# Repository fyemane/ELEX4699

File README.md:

# ELEX4699
ELEX4699 Elec System Design Project

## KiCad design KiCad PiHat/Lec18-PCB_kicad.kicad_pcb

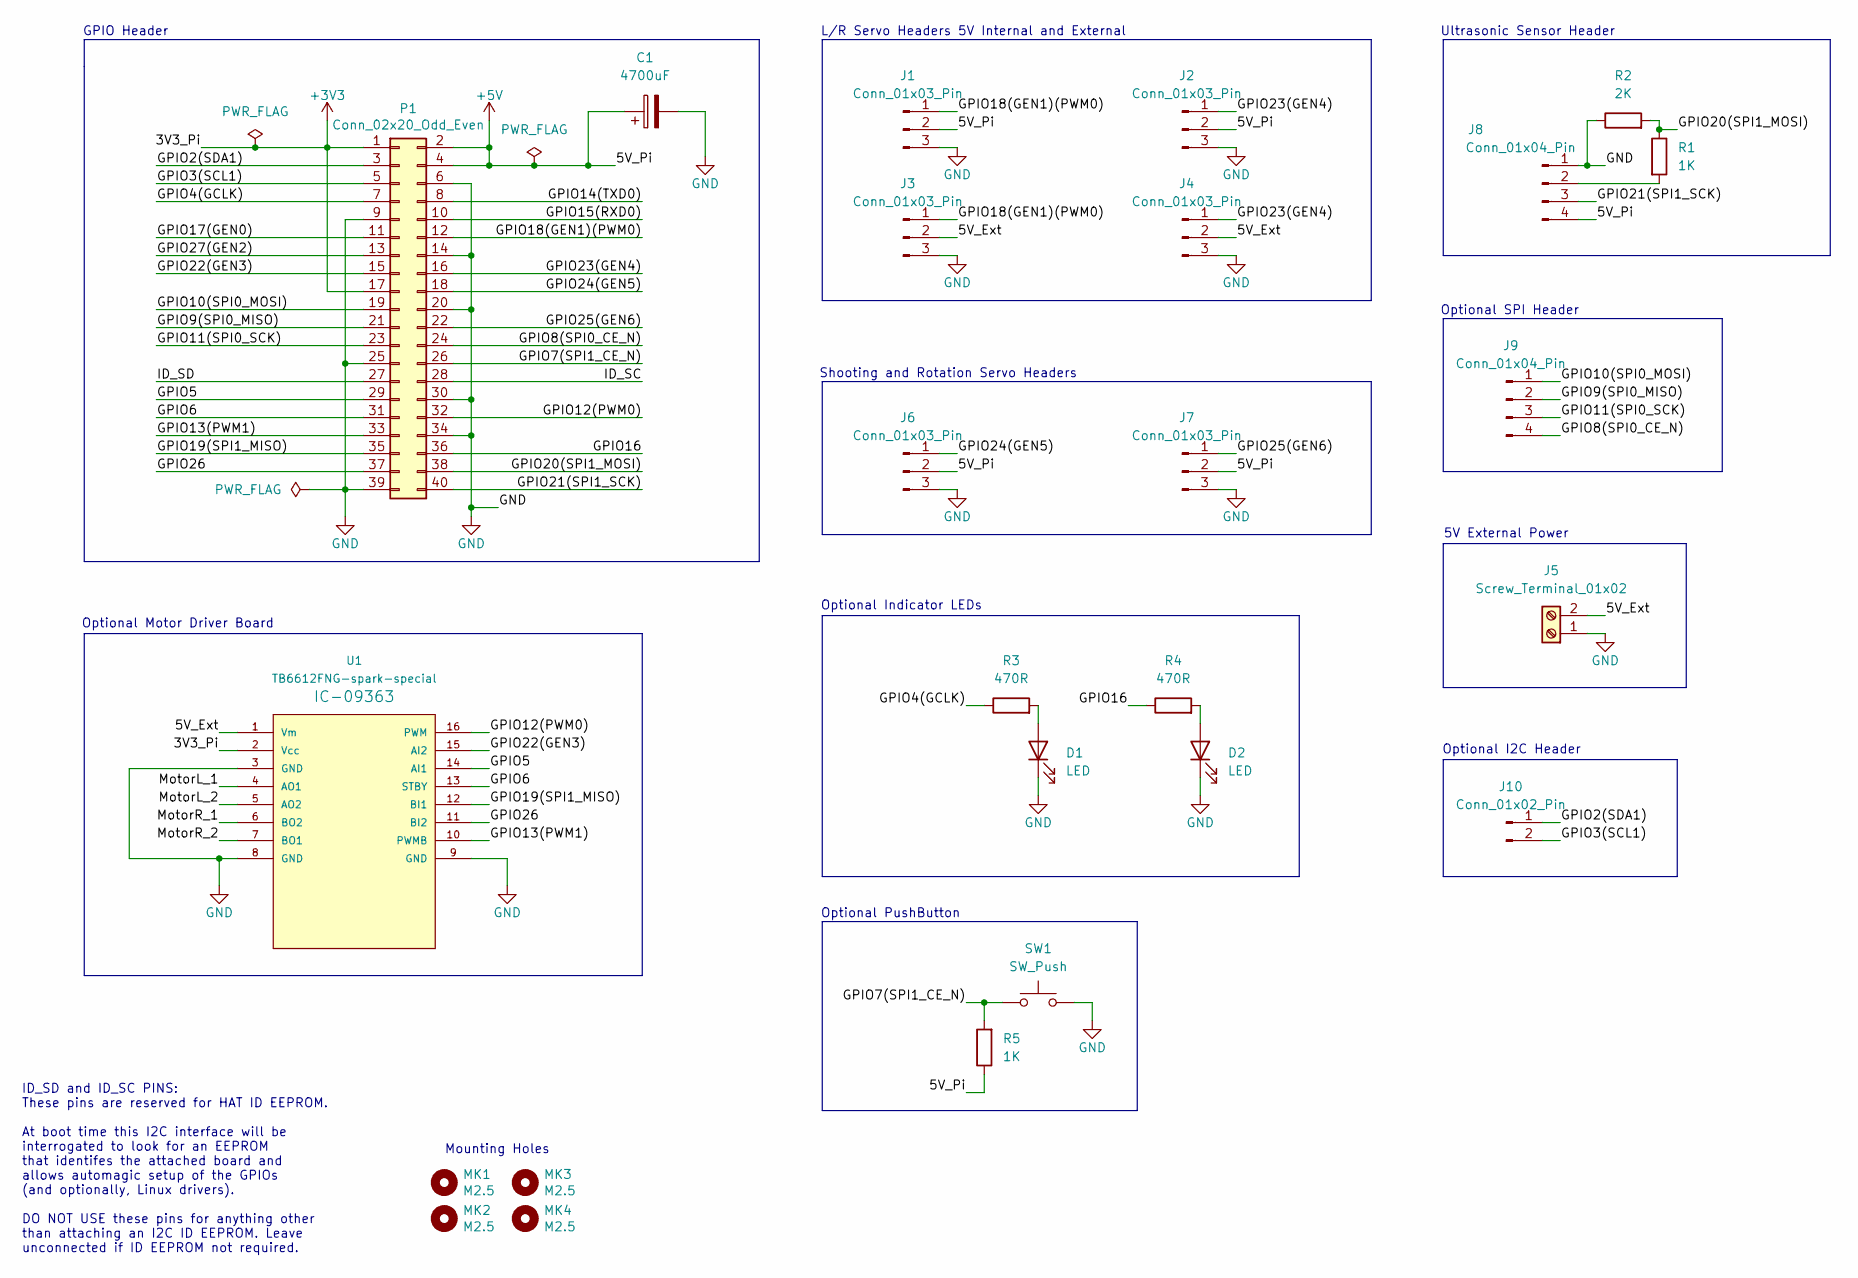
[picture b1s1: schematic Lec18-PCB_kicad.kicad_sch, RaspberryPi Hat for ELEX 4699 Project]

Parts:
C1: 4700uF; CP_Radial_D10.0mm_P7.50mm
D1, D2: LED; LED_D5.0mm
J1, J2, J3, J4, J6, J7: Conn_01x03_Pin; PinHeader_1x03_P2.54mm_Vertical
J5: Screw_Terminal_01x02; TerminalBlock_bornier-2_P5.08mm
J8, J9: Conn_01x04_Pin; PinHeader_1x04_P2.54mm_Vertical
J10: Conn_01x02_Pin; PinHeader_1x02_P2.54mm_Vertical
MK1, MK2, MK3, MK4: M2.5; MountingHole_2.7mm_M2.5
P1: Conn_02x20_Odd_Even; PinSocket_2x20_P2.54mm_Vertical
R1, R5: 1K; R_Axial_DIN0207_L6.3mm_D2.5mm_P10.16mm_Horizontal
R2: 2K; R_Axial_DIN0207_L6.3mm_D2.5mm_P10.16mm_Horizontal
R3, R4: 470R; R_Axial_DIN0207_L6.3mm_D2.5mm_P10.16mm_Horizontal
SW1: SW_Push; SW_PUSH_6mm_H5mm
U1: TB6612FNG-spark-special; MODULE_ROB-14450

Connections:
+3V3: P1.1, P1.17, U1.2 (Vcc)
+5V: C1.1, J1.2, J2.2, J6.2, J7.2, J8.4, P1.2, P1.4, R5.1
/5V_Ext: J3.2, J4.2, J5.2, U1.1 (Vm)
/GPIO2(SDA1): J10.1, P1.3
/GPIO3(SCL1): J10.2, P1.5
/GPIO4(GCLK): P1.7, R3.1
/GPIO5: P1.29, U1.14 (AI1)
/GPIO6: P1.31, U1.13 (STBY)
/GPIO7(SPI1_CE_N): P1.26, R5.2, SW1.1
/GPIO8(SPI0_CE_N): J9.4, P1.24
/GPIO9(SPI0_MISO): J9.2, P1.21
/GPIO10(SPI0_MOSI): J9.1, P1.19
/GPIO11(SPI0_SCK): J9.3, P1.23
/GPIO12(PWM0): P1.32, U1.16 (PWM)
/GPIO13(PWM1): P1.33, U1.10 (PWMB)
/GPIO14(TXD0): P1.8
/GPIO15(RXD0): P1.10
/GPIO16: P1.36, R4.1
/GPIO17(GEN0): P1.11
/GPIO18(GEN1)(PWM0): J1.1, J3.1, P1.12
/GPIO19(SPI1_MISO): P1.35, U1.12 (BI1)
/GPIO20(SPI1_MOSI): P1.38, R1.1, R2.2
/GPIO21(SPI1_SCK): J8.3, P1.40
/GPIO22(GEN3): P1.15, U1.15 (AI2)
/GPIO23(GEN4): J2.1, J4.1, P1.16
/GPIO24(GEN5): J6.1, P1.18
/GPIO25(GEN6): J7.1, P1.22
/GPIO26: P1.37, U1.11 (BI2)
/GPIO27(GEN2): P1.13
/ID_SC: P1.28
/ID_SD: P1.27
/MotorL_1: U1.4 (AO1)
/MotorL_2: U1.5 (AO2)
/MotorR_1: U1.6 (BO2)
/MotorR_2: U1.7 (BO1)
GND: C1.2, D1.1 (K), D2.1 (K), J1.3, J2.3, J3.3, J4.3, J5.1, J6.3, J7.3, J8.1, P1.6, P1.9, P1.14, P1.20, P1.25, P1.30, P1.34, P1.39, R2.1, SW1.2, U1.3 (GND), U1.8 (GND), U1.9 (GND)
unnamed: D1.2 (A), R3.2
unnamed: D2.2 (A), R4.2
unnamed: J8.2, R1.2

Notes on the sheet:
Optional SPI Header
Ultrasonic Sensor Header
Optional I2C Header
GPIO Header
L/R Servo Headers 5V Internal and External
5V External Power
ID_SD and ID_SC PINS: These pins are reserved for HAT ID EEPROM. At boot time this I2C interface will be interrogated to look for an EEPROM that identifes the attached board and allows automagic setup of the GPIOs (and optionally, Linux drivers). DO NOT USE these pins for anything other than attach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
Optional Motor Driver Board
Optional Indicator LEDs
Optional PushButton
Mounting Holes
Shooting and Rotation Servo Headers

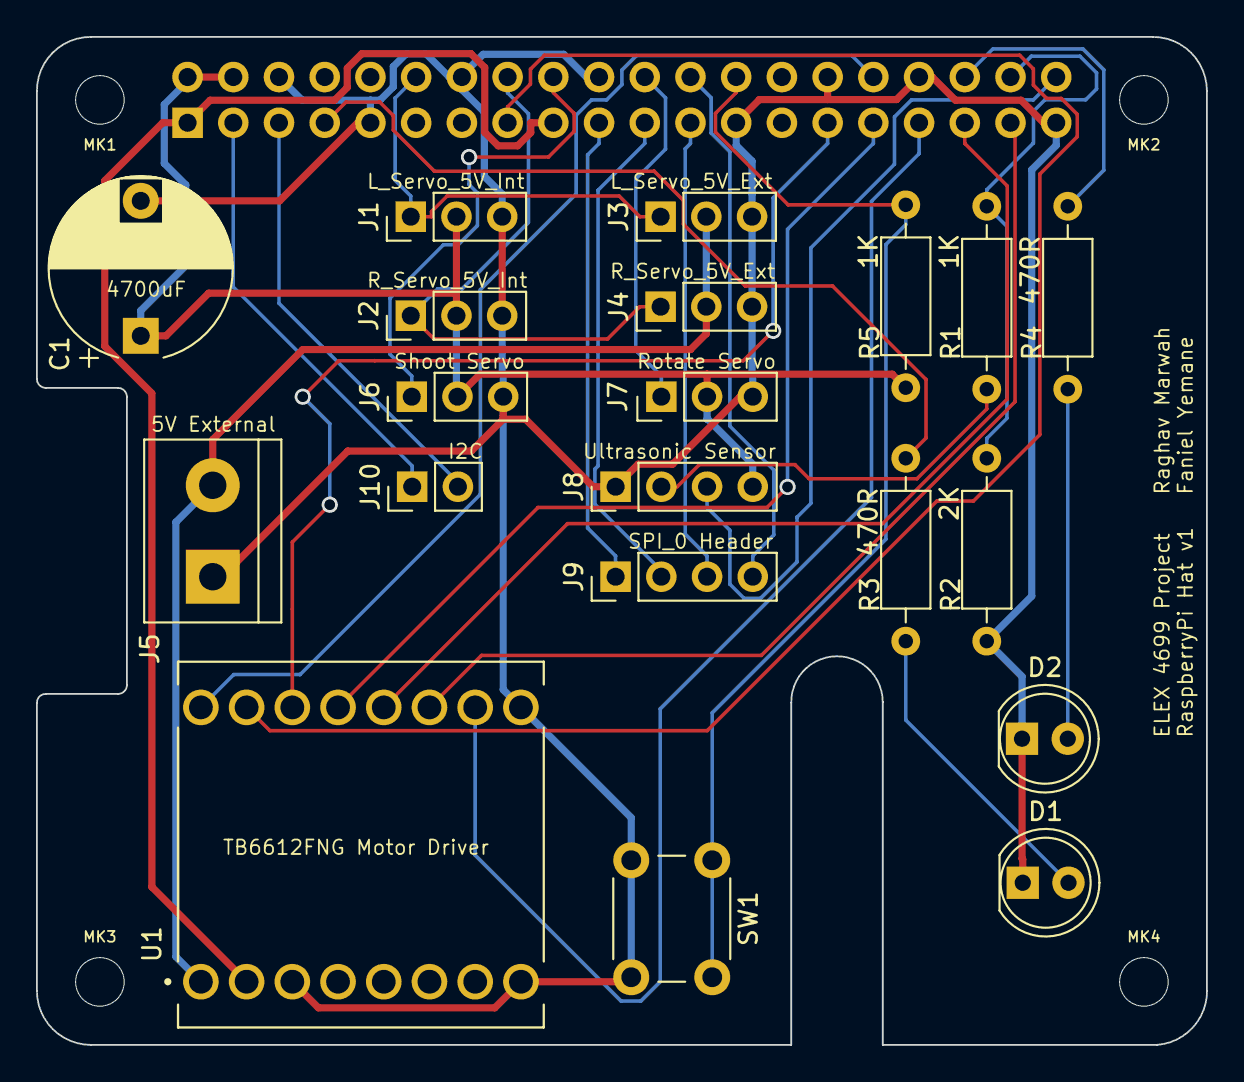
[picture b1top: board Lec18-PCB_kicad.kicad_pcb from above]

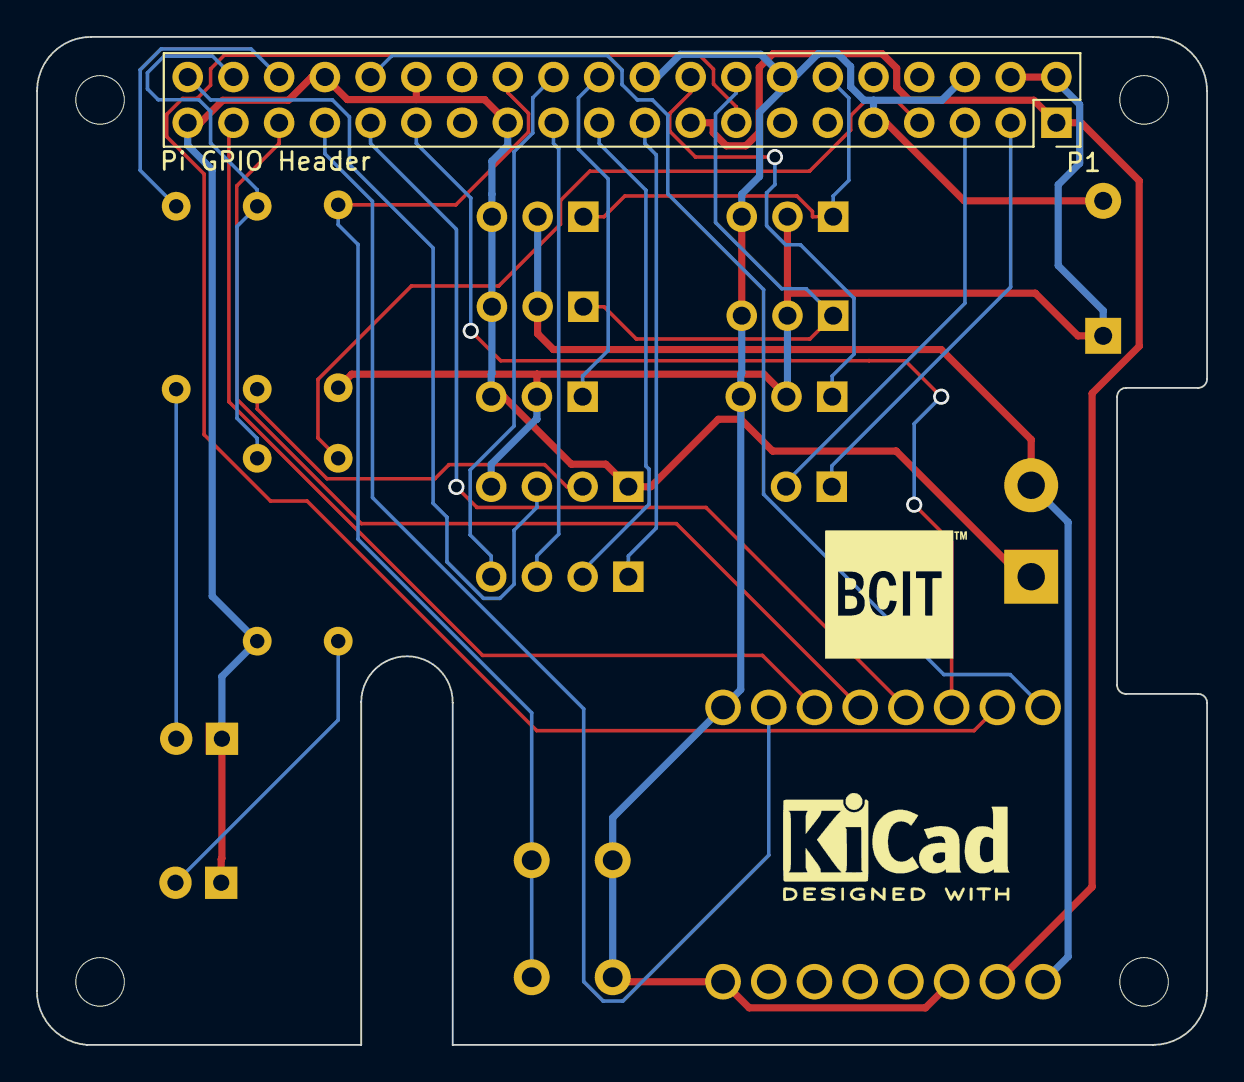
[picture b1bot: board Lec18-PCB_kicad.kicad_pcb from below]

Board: 2 copper layers, 65.0 x 56.0 mm, 26 parts (2 on the bottom side), 29 nets.

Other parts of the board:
G1: bcit_logo_small

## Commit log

2024-04-24 added pi and laptop code in progress
2024-04-26 adding files
2024-04-26 adding changes
2024-04-26 added ti mc firmware code
2024-04-26 Added 3D models
    Models for wheel connector and robot body.
2024-04-26 updating files, Milestone 1 completed
2024-04-27 created new branch to clean the Windows code
2024-04-27 Deleted unnecessary files.
2024-04-28 new header for ccontroller
2024-04-28 PCB Design completed, submitted for production.
2024-04-29 updated ccontroller, is now sending booserpack data to server
2024-04-29 fix bitwise operator error
2024-04-29 Fix some minor mistakes with the PCB design.
2024-05-01 get pi video feed and send drive commands, work in progress
2024-05-02 Updated 3D models
2024-05-03 updated pi code with shooter, laptop code with pi cam feed
2024-05-03 Updated and added 3D models.
2024-05-04 Corrected Pi IP address
2024-05-04 Updated 3D models.
2024-05-05 Experimental changes to picam
2024-05-11 Fixed robot movement when PiServer is started.
    Code cleanup, most up to date Pi Code with G1 rejection.
2024-05-11 Balanced F/R movement.
2024-05-11 Correct Forward speed
2024-05-11 updating teleop cams
2024-05-11 Able to communicate with xbox controller
2024-05-11 Working Xbox controller code
2024-05-11 Updated arena view
    Detailed arena view for teleop
2024-05-11 Small changes to xbox controller code
2024-05-11 Fix left/right control
2024-05-12 Code cleanup, deleted unneeded files.
2024-05-12 Update .gitignore file
2024-05-12 Ultrasonic sensor integrated with throttle control
2024-05-12 Minor bugfix with throttle stop code
2024-05-12 New cvui
    New cvui window for tuning
2024-05-12 bugfix hardvalue to variable.
2024-05-12 Fix Faniel's oopsies
2024-05-12 First test code for auto drive
2024-05-13 Aruco detection
    Aruco detection including center and area
2024-05-14 Big additions to autonomous driving logic
2024-05-15 Autonomous loop completed.
2024-05-16 Autonomous drive and shoot loop completed.
